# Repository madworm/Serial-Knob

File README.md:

Serial-Knob
===========

LAYOUT FILES: Rotary encoder + microcontroller. Sends commands via serial.

ATtiny25/45/85 + ALPS STEC12E08.

The microcontroller can evaluate direction of rotation, speed and acceleration + button status.
Depending on the requirements, this can be encoded in one single byte and sent to the target.

Step / direction decoding is also possible. By adding a multiplicator, this board could also
be used as a stepper-controller tester. Turn the knob, and the stepper should follow.

You will find code for this project in [this](https://github.com/madworm/ATtiny_projects/tree/master/85/Serial-Knob) repository.

---

Before having PC-boards made, please make sure you know about your manufacturer's peculiarities!
Especially drill-sizes and their tolerances may vary too much and give you trouble.

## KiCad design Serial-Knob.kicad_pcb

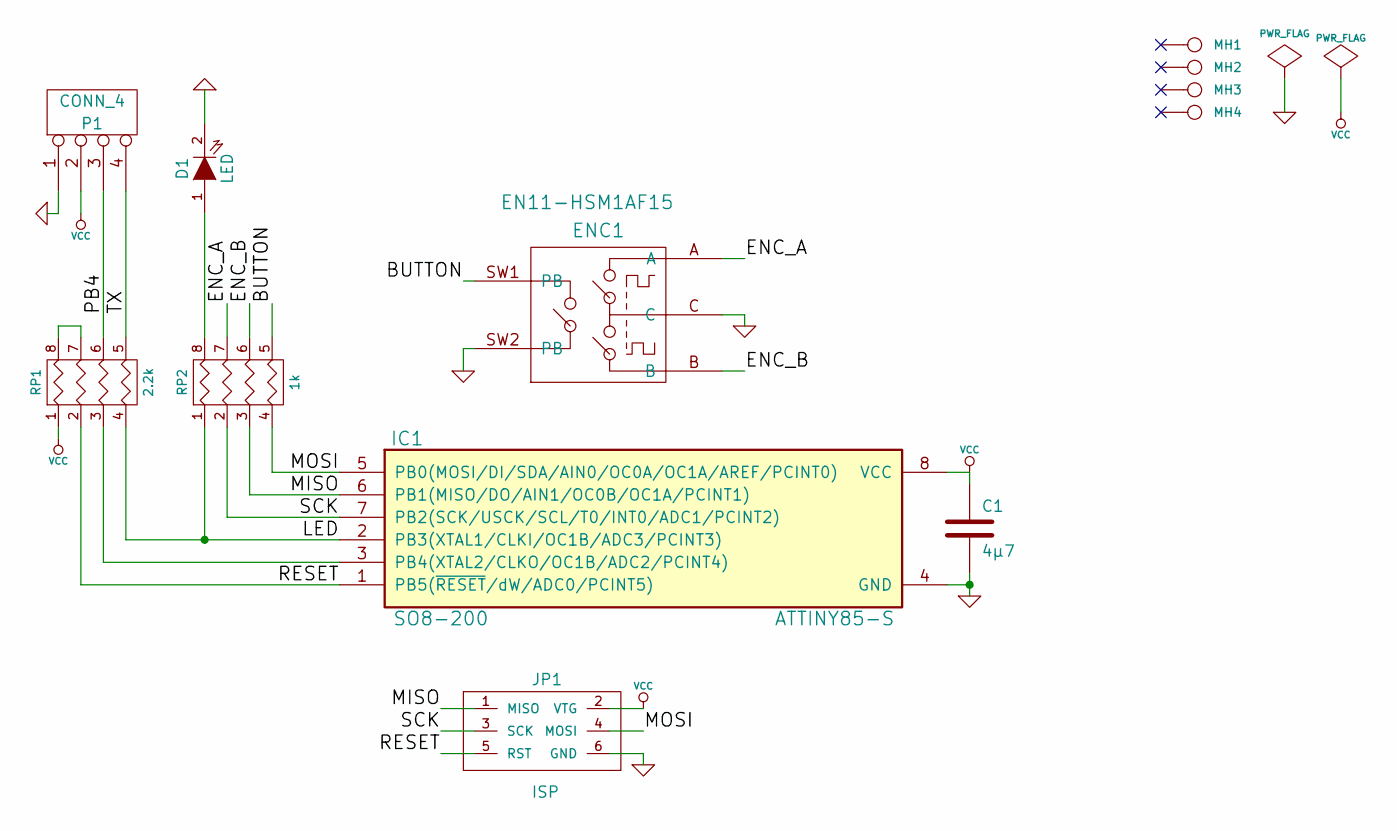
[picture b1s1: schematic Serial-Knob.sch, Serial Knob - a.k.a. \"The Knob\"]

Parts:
C1: 4µ7
D1: LED
ENC1: EN11-HSM1AF15
IC1: ATTINY85-S; SO8-200
JP1: ISP
MH1, MH2, MH3, MH4: CONN_1
P1: CONN_4
RP1: 2.2k
RP2: 1k

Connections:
/BUTTON: ENC1.SW1 (PB), RP2.5 (R4)
/ENC_A: ENC1.A, RP2.7 (R2)
/ENC_B: ENC1.B, RP2.6 (R3)
/LED: IC1.2 (PB3(XTAL1/CLKI/OC1B/ADC3/PCINT3)), RP1.4, RP2.1
/MISO: IC1.6 (PB1(MISO/DO/AIN1/OC0B/OC1A/PCINT1)), JP1.1 (MISO), RP2.3
/MOSI: IC1.5 (PB0(MOSI/DI/SDA/AIN0/OC0A/OC1A/AREF/PCI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), JP1.4 (MOSI), RP2.4
/PB4: P1.3, RP1.6 (R3)
/RESET: IC1.1 (PB5(~RESET~/dW/ADC0/PCINT5)), JP1.5 (RST), RP1.2
/SCK: IC1.7 (PB2(SCK/USCK/SCL/T0/INT0/ADC1/PCINT2)), JP1.3 (SCK), RP2.2
/TX: P1.4, RP1.5 (R4)
GND: C1.2, D1.2 (K), ENC1.C, ENC1.SW2 (PB), ENC1.body, IC1.4 (GND), JP1.6 (GND), P1.1
unnamed: IC1.3 (PB4(XTAL2/CLKO/OC1B/ADC2/PCINT4)), RP1.3
unnamed: RP1.7 (R2), RP1.8 (R1)
unnamed: D1.1 (A), RP2.8 (R1)
VCC: C1.1, IC1.8 (VCC), JP1.2 (VTG), P1.2, RP1.1

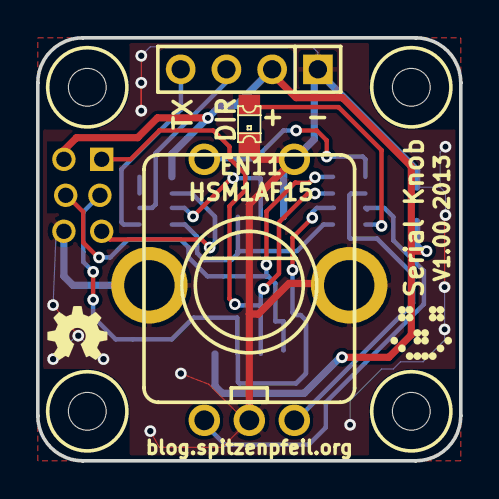
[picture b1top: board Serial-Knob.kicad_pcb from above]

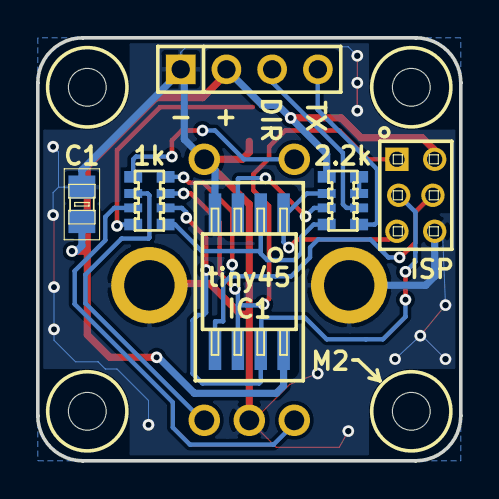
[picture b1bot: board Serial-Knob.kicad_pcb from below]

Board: 2 copper layers, 23.5 x 23.5 mm, 15 parts (5 on the bottom side), 15 nets.

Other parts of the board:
G1: OSHW_LOGO
G2: LED_SMILE
G3: TINDIE_DOG

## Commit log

2013-01-22 Blah.
2013-01-22 Had to modify the encoder footprint (no more slot holes).
2013-01-22 Tweaks.
2013-01-22 Rounded board edges are much nicer.
2013-01-22 Added website link to F_SilkS.
2013-01-22 Added a 6-pin ISP header - 2mm raster ;-(
2013-01-27 Removed obsolete text on B_SilkS.
2013-01-27 Added list of alternative parts.
2013-01-27 Switched to REV. 202 of atmel.lib
2013-01-27 0603 LED --> 0805 LED (as intended). Board 0.5mm wider + taller now.
2013-02-05 Made pin #1 of the ISP header rectangular.
2013-02-05 Added GND pour.
2013-02-11 Increased annular ring size for the SIL-4 header.
2013-02-13 Silkscreen updates + added version number.
2013-02-13 Updated 'README.md'
2013-02-13 Flipped ISP header to backside + tweaks.
2013-02-13 Silkscreen tweaks.
2013-02-15 Added some artwork to the front side ;-)
2013-02-18 Added some dimensions to the comment layer.
2013-02-23 Some behind the scenes stuff. Layout unchanged.
2013-02-26 Shifted ISP header pads. Attempt to keep the header from falling out.
2013-02-27 Silkscreen update.
2013-02-27 Updated 'README.md'.
2013-02-27 Changed the title of the worksheets (schematic + layout).
2013-02-28 Added a couple of GND-plane stitches.
2013-02-28 Made the mounting clip of the encoder GND as well.
2013-02-28 Made the stitching-vias smaller.
2013-02-28 All R0603 --> R0805. Much faster to assemble.
2013-02-28 Shifted some tracks for better GND plane flow.
2013-03-01 Changed all vias to 0.65/0.35 + moved to 1206 resistor packs (4x).
2013-03-01 Tweaks + recreate gerbers.
2013-03-01 Eliminated reset pullup by using unused rpack pins + now one 2.2k rpack.
2013-03-01 Moved some vias + traces.
    Now there's enough room to move the mounting holes inwards a bit. That
    way the encoder footprint is easily switched from EN12 types to EN11.
2013-03-01 Found a via that interfered with silkscreen text.
2013-03-02 ENC footprint made to fit EN11-HSM1AF15. Need to do it properly later.
2013-03-02 Switched footprint to MADW__EN11-HSM1AF15. All proper now.
2013-03-02 Moved the LED a bit farther away from the encoder knob.
2013-03-03 Moved ISP header a bit away from board edge + shifted some vias.
2013-03-03 A shifty business with vias. 'Tindie' is now back on the .gts layer.
2013-03-04 Upped version number to 1.00
2013-03-05 Made a 4x4 'panel'.
2013-03-05 Added more drills to the break-away tabs.
2013-03-05 Some routing arcs were a bit off.
2013-03-06 Changed the break-away tabs for the 4x4 panel.
2013-03-06 Added 2 PNGs for the 4x4 panel.
2013-03-08 Forgot board ID + date on 4x4 panel.
2013-03-20 Replaced all the NPTH holes with "mouse-byte" footprints.
2013-03-21 Fixed a typo.
2013-03-23 Updated the 4x4 panel to newer mouse-bite footprint.
2013-03-23 Recreated the 4x4-panel gerber files.
2013-03-27 Renamed a few files to fit new KiCad layer naming.
2013-03-27 Recreated some gerber files.
2013-03-27 Updated the 4x4 panel to NPTH mounting holes as well.
2013-03-27 Recreated some gerber files for the 4x4 panel.
2013-05-16 4x4 panel: for some reason the F.Paste / B.Paste layers were missing.
2013-05-16 4x4 panel: updated the gerber files as well (missing paste layers).
2013-06-27 Converted to new kicad board format.
2013-09-17 Fixed missing module definitions (pcbnew BZR 4319 was barfing).
